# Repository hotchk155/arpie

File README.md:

arpie
=====

MIDI Arpeggiator

http://www.youtube.com/watch?v=mk7zSJ8mq2A

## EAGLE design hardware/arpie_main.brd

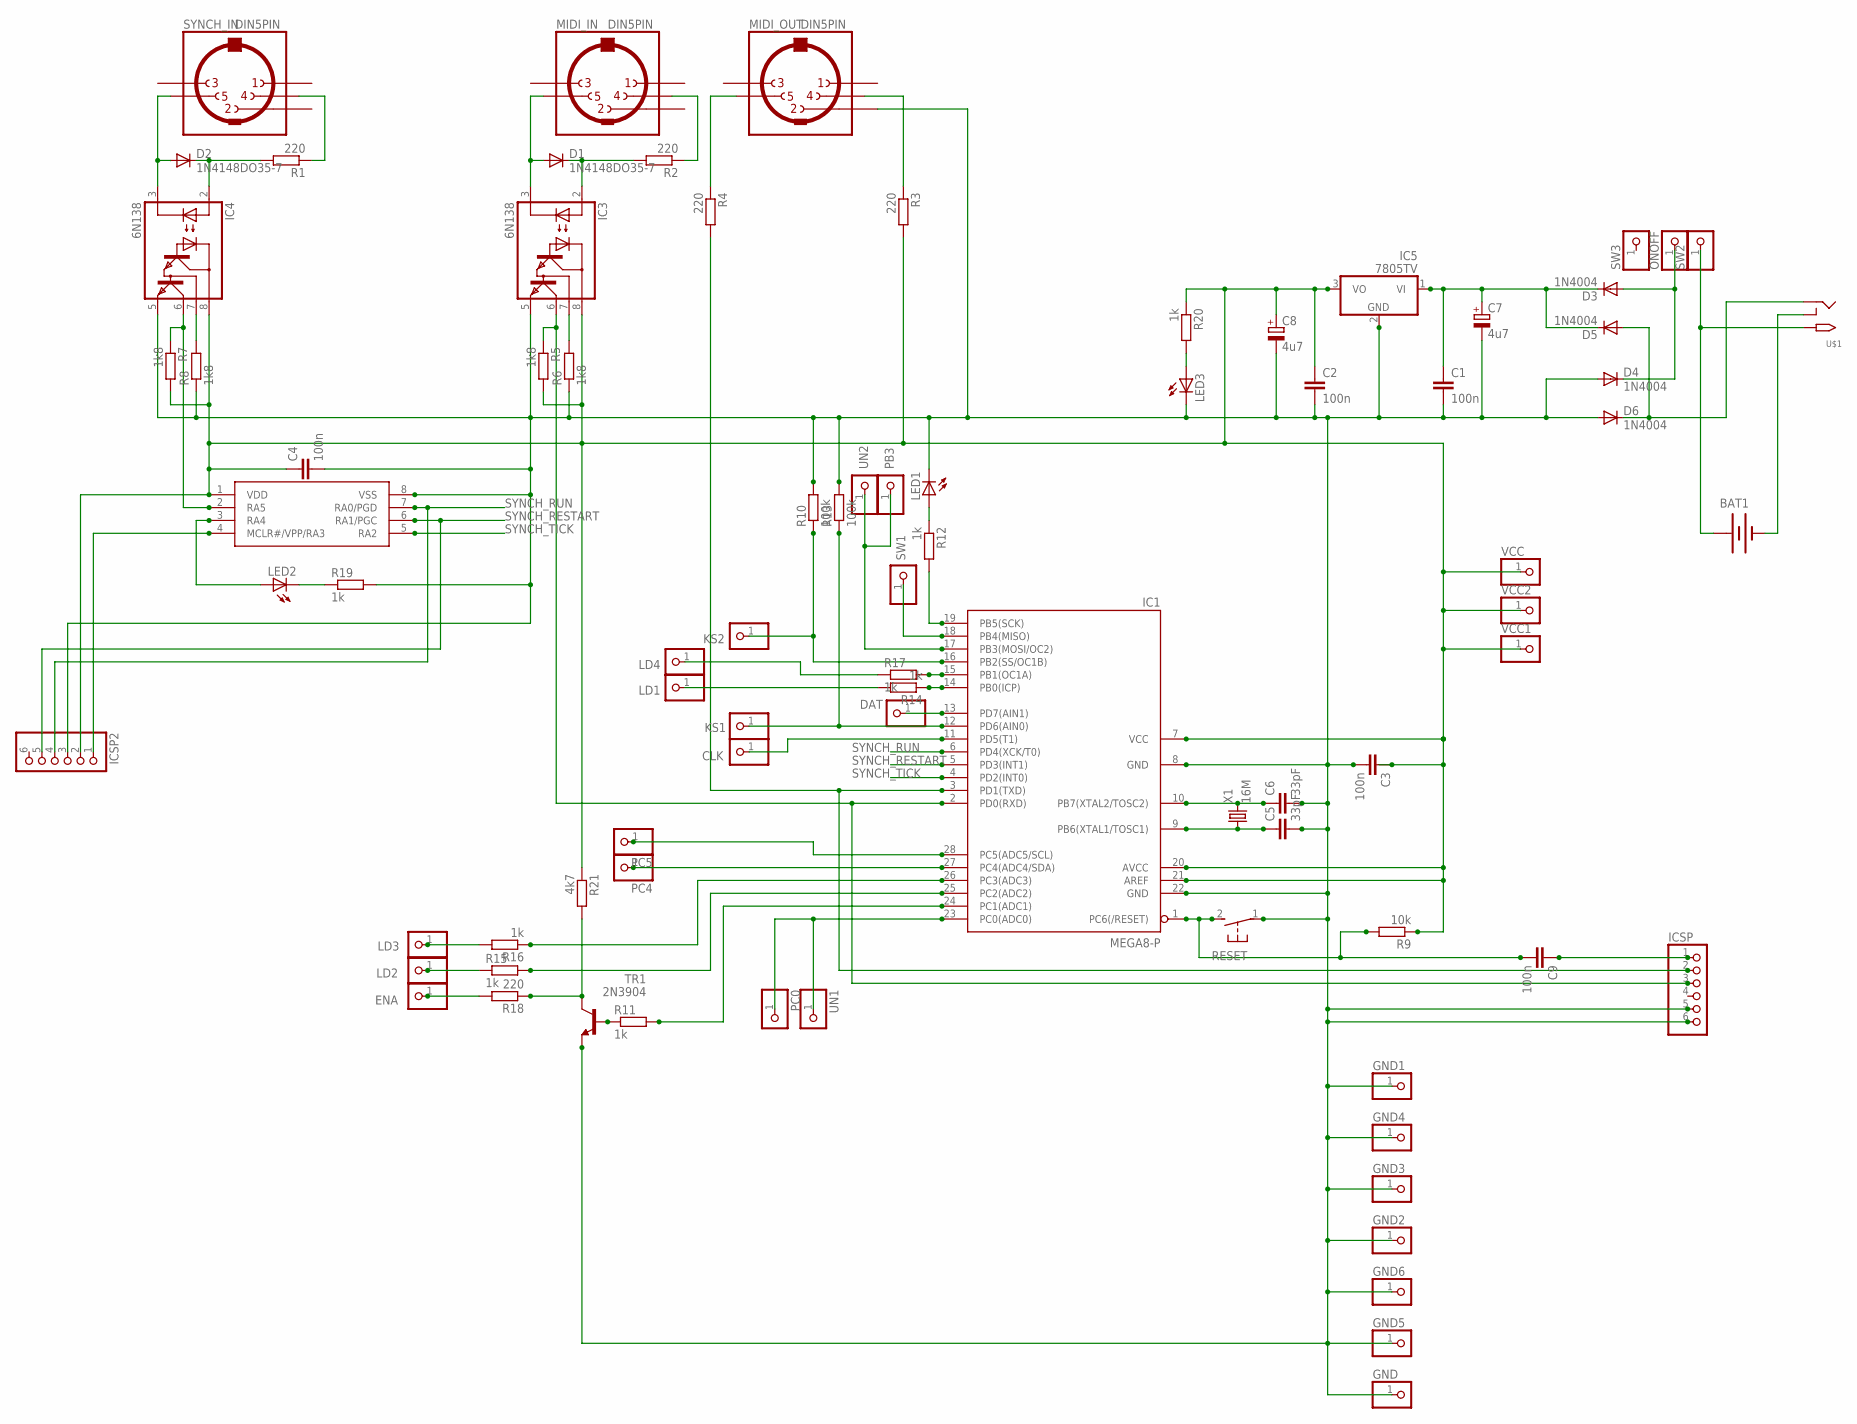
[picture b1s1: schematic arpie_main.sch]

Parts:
BAT1: BATTERY; PP3_BATTERBOX
C1, C2, C3, C4, C9: 100n; C025-024X044
C5, C6: 33pF; C025-024X044
C7, C8: 4u7; E2,5-7
CLK: PINHD-1X1; 1X01
D1, D2: 1N4148DO35-7; DO35-7
D3, D4, D5, D6: 1N4004; DO-VERT
DAT: PINHD-1X1; 1X01
ENA: PINHD-1X1; 1X01
GND, GND1, GND2, GND3, GND4, GND5, GND6: PINHD-1X1; 1X01
IC1: MEGA8-P; DIL28-3
IC2: PIC12F1822; DIL08
IC3, IC4: 6N138; DIL08
IC5: 7805TV; TO220V
ICSP, ICSP2: PINHD-1X6; 1X06
KS1, KS2: PINHD-1X1; 1X01
LD1, LD2, LD3, LD4: PINHD-1X1; 1X01
LED1, LED2, LED3: LED3MM
MIDI_IN: DIN5PIN; RAPIDDIN5
MIDI_OUT: DIN5PIN; RAPIDDIN5
ONOFF: PINHD-1X1; 1X01
PB3: PINHD-1X1; 1X01
PC0, PC4, PC5: PINHD-1X1; 1X01
R1, R2, R3, R4: 220; 0207/7
R5, R6, R7, R8: 1k8; 0207/7
R9: 10k; 0207/7
R10: 100k; 0207/7
R11, R12, R19, R20: 1k; 0207/7
R13: 100k; 0207/2V
R14, R15, R16, R17: 1k; 0207/2V
R18: 220; 0207/2V
R21: 4k7; 0207/2V
RESET: 31-XX; B3F-31XX
SW1, SW2, SW3: PINHD-1X1; 1X01
SYNCH_IN: DIN5PIN; RAPIDDIN5
TR1: 2N3904; TO92
U$1: 2.1MMJACKTHM; PJ-102A
UN1, UN2: PINHD-1X1; 1X01
VCC, VCC1, VCC2: PINHD-1X1; 1X01
X1: 16M; HC49/S

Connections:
CLK: CLK.1, IC1.11 (PD5(T1))
DAT: DAT.1, IC1.13 (PD7(AIN1))
ENA: ENA.1, R18.2
GND: C1.2, C2.2, C3.2, C4.2, C5.2, C6.2, C7.-, C8.-, D4.A, D6.A, GND.1, GND1.1, GND2.1, GND3.1, GND4.1, GND5.1, GND6.1, IC1.8 (GND), IC1.22 (GND), IC2.8 (VSS), IC3.5 (GND), IC4.5 (GND), IC5.2 (GND), ICSP.5, ICSP.6, ICSP2.3, LED1.K (C), LED3.K (C), MIDI_OUT.2, R6.1, R8.1, R10.2, R13.2, R19.2, RESET.1, TR1.3 (E)
KS1: IC1.12 (PD6(AIN0)), KS1.1, R13.1
KS2: IC1.16 (PB2(SS/OC1B)), KS2.1, R10.1
LD1: LD1.1, R14.2
LD2: LD2.1, R15.1
LD3: LD3.1, R16.2
LD4: LD4.1, R17.1
unnamed: D1.A, IC3.3 (C), MIDI_IN.5
unnamed: D1.C, IC3.2 (A), R2.2
unnamed: MIDI_IN.4, R2.1
unnamed: D2.A, IC4.3 (C), SYNCH_IN.5
unnamed: D2.C, IC4.2 (A), R1.2
unnamed: R1.1, SYNCH_IN.4
unnamed: IC1.2 (PD0(RXD)), IC3.6 (VO), ICSP.3, R5.1
unnamed: IC3.7 (VB), R6.2
unnamed: C9.1, ICSP.1
unnamed: IC4.7 (VB), R8.2
unnamed: MIDI_OUT.5, R4.1
unnamed: IC1.3 (PD1(TXD)), ICSP.2, R4.2
unnamed: MIDI_OUT.4, R3.1
unnamed: R18.1, R21.2, TR1.1 (C)
unnamed: IC2.2 (RA5), IC4.6 (VO), R7.1
unnamed: IC2.3 (RA4), LED2.A
unnamed: IC1.28 (PC5(ADC5/SCL)), PC5.1
unnamed: IC2.4 (MCLR#/VPP/RA3), ICSP2.1
unnamed: LED3.A, R20.2
unnamed: IC1.27 (PC4(ADC4/SDA)), PC4.1
unnamed: D5.A, D6.C, U$1.RING
unnamed: R11.1, TR1.2 (B)
unnamed: IC1.26 (PC3(ADC3)), R16.1
unnamed: C6.1, IC1.10 (PB7(XTAL2/TOSC2)), X1.2
unnamed: C5.1, IC1.9 (PB6(XTAL1/TOSC1)), X1.1
unnamed: C9.2, IC1.1 (PC6(/RESET)), R9.2, RESET.2 (S)
unnamed: IC1.25 (PC2(ADC2)), R15.2
unnamed: IC1.24 (PC1(ADC1)), R11.2
unnamed: IC1.14 (PB0(ICP)), R14.1
unnamed: IC1.19 (PB5(SCK)), R12.2
unnamed: LED1.A, R12.1
unnamed: LED2.K (C), R19.1
unnamed: D3.A, D4.C, ONOFF.1
unnamed: IC1.15 (PB1(OC1A)), R17.2
unnamed: BAT1.0V (-), U$1.RING_SW
PWR+: BAT1.9V (+), SW2.1, U$1.TIP
SW1: IC1.18 (PB4(MISO)), SW1.1
SYNCH_RESTART: IC1.5 (PD3(INT1)), IC2.6 (RA1/PGC), ICSP2.5
SYNCH_RUN: IC1.6 (PD4(XCK/T0)), IC2.7 (RA0/PGD), ICSP2.4
SYNCH_TICK: IC1.4 (PD2(INT0)), IC2.5 (RA2)
UN1: IC1.23 (PC0(ADC0)), PC0.1, UN1.1
UN2: IC1.17 (PB3(MOSI/OC2)), PB3.1, UN2.1
VCC: C2.1, C3.1, C4.1, C8.+, IC1.7 (VCC), IC1.20 (AVCC), IC1.21 (AREF), IC2.1 (VDD), IC3.8 (VCC), IC4.8 (VCC), IC5.3 (VO), ICSP2.2, R3.2, R5.2, R7.2, R9.1, R20.1, R21.1, VCC.1, VCC1.1, VCC2.1
VIN: C1.1, C7.+, D3.C, D5.C, IC5.1 (VI)

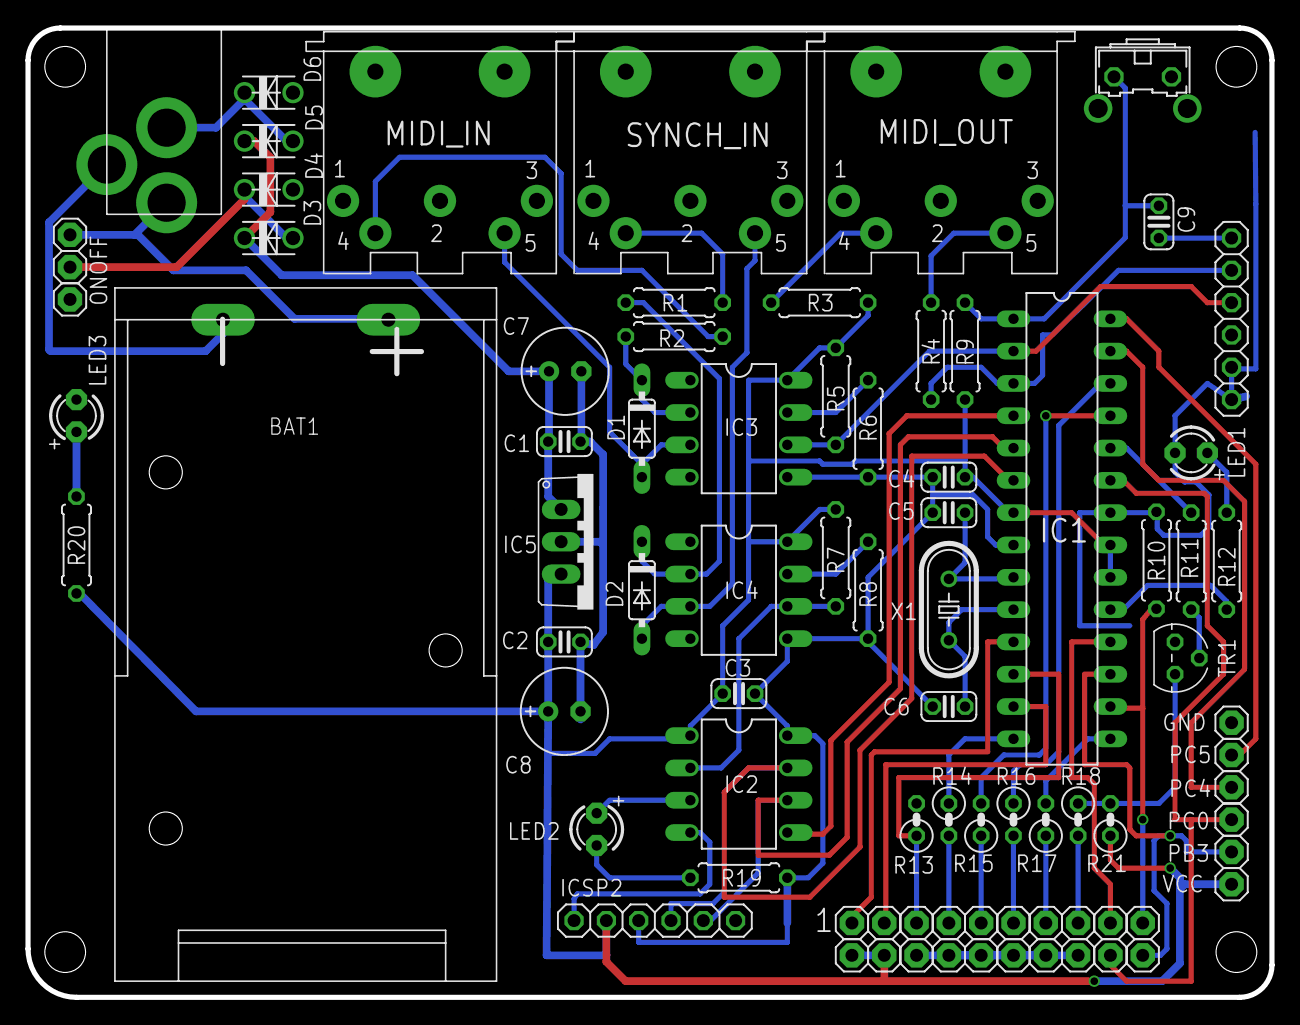
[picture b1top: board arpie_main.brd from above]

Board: 2 copper layers, 97.8 x 76.2 mm, 83 parts (0 on the bottom side), 54 nets.

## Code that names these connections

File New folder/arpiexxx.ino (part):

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#define P_UI_OUT_LED     17
#define P_UI_HOLD_LED     9

#define P_UI_CLK     5   //PD5
#define P_UI_DATA    7   //PD7
#define P_UI_STROBE  15  //PC1
#define P_UI_READ1   10  //PB2
#define P_UI_READ0   6   //PD6

#define DBIT_UI_CLK     0b00100000  // D5
#define DBIT_UI_DATA    0b10000000  // D7
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#define SYNCH_HOLD_AT_ZERO             0x0080    // This flag resets and suspends arpeggiator while still passing MIDI clock
//#define SYNCH_RESTART_NEXT_STEP        0x0100    // Signals for a deferred restart at the next beat
#define SYNCH_BEAT_LED                 0x2000    // Beat signal
#define SYNCH_RESTART                  0x4000    // Flag signals that arpeggiator should restart
#define SYNCH_STEP                     0x8000    // Flag signals that arpeggiator should advance to next step


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    pinMode(14, INPUT);
    pinMode(19, INPUT_PULLUP);
    delay(10);
    if(!(PINC & (1<<5))) // PC5 pulled low means synchtab present
    {    
      synchClockSendState = SYNCH_HH_EXT_CLOCK;  // disable clock output
      PCICR |= (1<<1);                           // enable pin change interrupt 1
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    The template parameter determines if the CV is controlled by note 
 pitch(false) or note velocity(true)
 
 11  PB3 clkout
 14  PC0 gateout
 */
template<boolean VEL_MODE> 
class CCVTabDriver : 
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
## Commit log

2013-03-05 tweaks
2013-03-20 part values
2013-03-20 initial commit of updated firmware
2013-03-25 tweaks an d bug fixes
2013-03-25 images added
2013-03-30 fix issue with held note count
2013-04-02 improvement to start of bar synch logic
2013-04-02 allow UI to handle long keypress function
2013-04-02 improvements to midi thru handling
2013-04-03 improve downstream midi slave synch capability
2013-04-03 Rev 2 changes
    increase spacing of DIN connectors
    move reset button and DC socket
    larger holes for 3x6mm tact switches
    text changes
2013-04-04 updates for pcb manuf
2013-04-04 midi thru fixes/manual velocity
2013-04-08 manual
2013-04-08 New goodies
    EEPROM save for synch/channel params
    Allow full step gate length without tie
    changes to SYNC tempo display
    Add tap tempo function
2013-04-09 docs updates
2013-04-16 tidying up
2013-04-16 Fixes and enhancments
    Allow f/w version to be displayed by pressing HOLD when switching on
    Correct order of note rates
2013-04-18 quick ref
2013-04-21 1.01 passthru options
2013-04-22 Adding control over synch source
2013-04-23 add input lock mode via hold button
2013-04-26 1.02 header
2013-04-26 clear held chord info when changing input channel
2013-04-26 quick enhancements
    1. Improve BPM accuracy
    2. Allow forwarding of non-note channel messages on selected input
    channel to selected output channel to be controlled
2013-04-26 photos
2013-04-26 image edits
2013-05-13 V1.03
    Fix issue with synch thru/change lockout blink rate
2013-05-13 Fix issue with synch thru/change lockout blink rate
2013-05-13 synch passthru fixes
2013-05-14 updates for 1.03
2013-05-14 external synch tweaks
2013-05-19 pics
2013-05-19 tidy
2013-05-19 wiki updates
2013-05-19 documentation updates
2013-05-19 wishlist
2013-05-27 move wishlist to issues
2013-06-09 docs
2013-06-14 images from Dave for Clock mod
2013-06-14 daves clock mod
2013-06-17 simon's case mod
2013-06-18 simons case
2013-09-15 Updates to packing slip
2013-09-23 Chore: Fix small typo in docs
2013-11-05 gitignore
2013-11-06 Reflect main board rev 3
2013-11-08 rev3 board images
2013-11-08 image
2013-11-09 Flickerfix image
2014-01-04 big arpie
2014-01-04 arpiemax gitignore
2014-03-25 reduce flicker of dim level led
2014-04-29 INPUT_PULLUP
2015-02-14 // 99.99 07Feb14 Midi CC filter
2015-02-14 A4 release candidate
2015-02-14 New docs for v4
2015-02-14 more docs
2015-02-14 Order HH pot options like controltab reference design and tweak couple of other settings
2015-02-18 add back 1.3 docs
2015-02-18 update docs
2015-02-21 ain't monophonic no more!
2015-03-02 case files
2015-03-02 twin
2015-04-27 new stuff
2015-04-27 move gitignore
2015-04-27 move mainboard v3 to master
2015-04-27 grounded MIDI output, add LED pullup
2015-05-23 board rev4
2015-07-08 ecp file added
2015-08-31 Hack header refactoring, CV tab support
2016-01-22 working on changes
2016-01-22 stuff
2016-02-07 release folder for a4 version
2016-02-07 case bom
2016-02-07 Revert "case bom"
    This reverts commit 0e90100c6aa9195a14de3ad34ee7f7b512132dd1.
2016-02-07 Revert "release folder for a4 version"
    This reverts commit a174c12ba82b676ab2407660ba167d03930e1b3d.
2016-06-03 changes for transpose sequence/manual chord
2016-06-04 new patn layers
2016-07-19 more changes
2016-09-07 Volca FM CC mode
2016-09-07 Use syncFlags bits for all synch module status instead of byte variables
2016-09-07 adjustable accent velocity
2017-01-30 local off
2017-05-22 v5 quick ref
2017-06-15 bits
2017-06-18 Release candidate 5
2017-06-18 Release A5
2017-07-18 create release A5 folder
2017-07-18 adding branch for 5.1
2017-07-23 naming
2018-01-10 case mods
2018-01-12 upds
2018-03-11 5.2
    rel 5.2 - fix timing glitch on aux sync
2018-03-11 updated release folder
2018-05-14 Added preference to disable MIDI Running Mode
2018-07-05 case
2018-11-30 support clock function of cvtab
2018-12-09 support cv/gate on cvtab
2018-12-09 do not pass notes thru in midi transpose mode
2018-12-09 poly aftertouch
2018-12-15 Added "use note off" option
2018-12-15 bundle arp as a patch
2018-12-23 shift by hold button
2019-01-11 working on eeprom functions
2019-01-11 hack header mode set at startup/blink leds in patch mode
2019-01-11 just some moving around
2019-01-13 calibration function for cvtab
2019-01-13 storage of calibration data on cvtab
2019-01-13 refactor cv/gate control
2019-02-01 5.2 hex
2019-02-24 case instructions from old web site
2019-03-05 work in progress for v6
2019-03-05 initial release notes
2019-03-13 Glide working
2019-03-27 tab end
2019-04-25 change pattern layer functionality
2019-04-25 allow accent output on CVTab clock out
2019-04-25 sweep bug fix
2019-04-25 fixes to pitch glide
2019-04-25 test v 5.55
2019-05-22 6.0.1beta
2019-05-22 5.3beta - proper name
2019-06-08 5.4 BETA with bug fixes
    avoid all attempts to access CVTab unless in the correct mode
2019-06-17 change to way active pattern layer is selected
2019-06-17 hzvolt support
2019-07-26 5.7BETA - Step advance mode
2019-07-27 5.7beta with fix for step length
2019-07-27 LED profile tweak / accent+glide triggered only on real step
2019-07-27 v5.8
2019-07-27 5.9 - random2 mode
2019-07-27 5.9 release notes
2019-09-13 v6 manual
2019-09-13 images
2019-09-14 tere
2019-09-14 dewrf
2019-09-16 init patch
2019-09-16 5.10 init patch/indicate last patch
2019-09-17 fix dupe lines lg 5mm
2019-09-17 dsdd
2019-09-22 fix send clock LED issue
2019-09-22 ensure tick to pulse ratio also used on ext clock in
2019-09-22 resync button
2019-09-23 update release notes
2019-09-23 Version 6.0
2019-09-26 typos
2019-11-05 Revert "Update arpie.ino"
    This reverts commit 1b937bc56bd1caa416f44e9dfce60e194e3457db.
2019-11-05 V6.1
2020-01-08 update packing slip
2020-04-24 bom update
2020-09-22 move readme
2021-04-12 case tweaks
